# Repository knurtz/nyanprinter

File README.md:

# NyanPrinter
This printer runs on STM32F103 and it prints AND plays the nyan cat!

## Idea

Thermal printers make a lot of noise while printing -- everyone, who has bought something from a shop with one of those old cash registers knows that! At the heart of such a printer lies of course a stepper motor. Making music with stepper motors is an old thing in the Arduino community. But as far as I know, nobody has ever tried to make music AND print something at the same time -- until now!

Getting picture and sound to line up is not particulary easy, because there are certain limitations to the printing speed of a thermal printer -- and thus also for the maximum pitch we can get out of the machine. 

The datasheet recommends an approximate exposure of 1 ms per line, which responds to a 1 kHz pitch. This is, unless more than 64 pixels out of the total 384 pixels per line are printed simultanously. Here we need to do devided printing, which means multiple exposure bursts for one single line. This is where things get tricky. I need to let the printer run at a fixed speed and cannot stop at a line just because I want to print more than 64 pixels. Otherwise I would get a sudden break in my music.

This is the solution I came up with: If the printer encounters a line with more than 64 pixels, it prints the first 64 (or less) pixels, then advances the motor one step, going back one step immediately in order to print the next 64 pixels and so on. I have not yet tested, if the sudden change in direction is audible. If so, I might have to change it up a little bit and print multiple lines first, then go back over them a second time.

## Hardware

- STM32F103 Bluepill Development Board: [stm32duino.com](https://web.archive.org/web/20190524151648/https://wiki.stm32duino.com/index.php?title=Blue_Pill)
- Thermal printer MATSUSHITA EPL1801S2E from [pollin.de](https://www.pollin.de/p/thermo-druckelement-matsushita-epl1801s2e-721066)
- an awesome huge blue push button from [Amazon](https://www.amazon.de/gp/product/B07BSFMZJ2) (it lights up, too!)
- A4988 stepper motor driver board like this one from [pololu.com](https://www.pololu.com/product/1182)
- RECOM R-78E5.0-0.5 DC/DC converter from [conrad.de](https://www.conrad.de/de/recom-r-78e50-05-dcdc-wandler-print-24-vdc-5-vdc-500-ma-anzahl-ausgaenge-1-x-157954.html?)
- MAX6966 led driver from [farnell.com](https://de.farnell.com/maxim-integrated-products/max6966aee/led-treiber-mit-i-o-erweiterung/dp/2516036) for fancy led stuff
- custom milled PCB with some additional components like resistors and capacitors (Eagle files following shortly)
- custom enclosure printed with the amazing Vertigo Starlight filament from [filamentworld.de](https://www.filamentworld.de/shop/pla-filament-3d-drucker/pla-filament-1-75-mm-vertigo-starlight-075-kg/) (STL files following shortly as well)

## Software

I wanted to learn more about hardware peripherals of the STM32 family in this project. This is why I use a total of 3 timers, 2 DMA channels, one SPI and one UART peripheral. Things could have probably be done less complicated, but I would not have learned anything the easy way.

TIM2 is responsible for the motor step signal. It runs at a frequency that is determined by the current pitch of the music. The motor driver makes a step at every rising edge of the signal. Also, the printer needs to advance two steps for every line. Because of that, at every update interrupt of TIM2 (which corresponds to every step of the motor) I alternate between sending new data to the printer (triggering TIM1) and starting the exposure (triggering TIM3).

Data transfer is timed by TIM1, which triggers 64 DMA requests (64 transfers * 6 "pixels" per transfer = 384 pixels per line). The DMA sends the data to 6 parallel data lines that go into 6 shift registers inside the printer. Data alignment looks weird, this is why I wrote a small python script to convert images to a special byte array.

Finally TIM3 creates a pulse that corresponds to the needed exposure time of about 750 - 1000 us (depending on the supply voltage).

UART is needed for debugging and SPI for the led driver.

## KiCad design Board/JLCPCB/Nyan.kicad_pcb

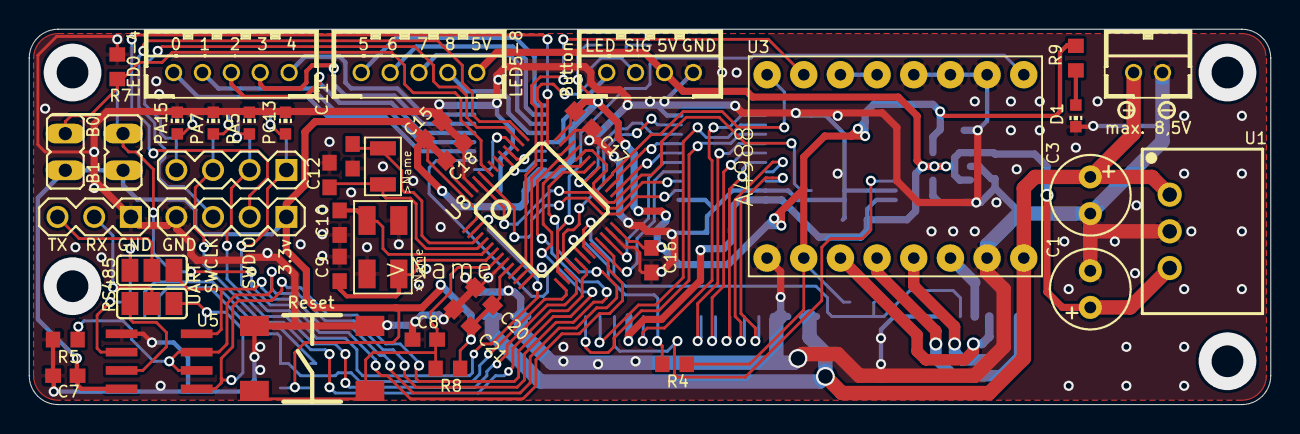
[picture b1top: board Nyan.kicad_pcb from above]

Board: 2 copper layers, 86.0 x 26.0 mm, 66 parts (0 on the bottom side), 75 nets.

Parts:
C1, C3: 100u; E2,5-6
C2, C14, C21: 1u; C0603
C4, C5, C6, C7, C8, C15, C16, C17, C18, C20, C22: 100n; C0603
C9, C10: 30p; C0603
C11, C12: 15p; C0603
C13: 22n; C0603
C19: 10u; C0603
D1, D2, D3, D4, D5: CHIP-LED0603
JP1, JP2: JP1
Q1: 8M; SMD_5X3.2
Q2: 32768; SMD_3.2X1.5
R1: 300; R0603
R2: 47k; R0603
R3, R4, R5, R6, R7, R8, R9, R10, R11, R12, R13, R14: 10k; R0603
S1: 6X6_MOMENTARY_SWITCH
SJ1, SJ2: SJ_2
SV2, SV3: MA04-1_ROUND
U1: R-78C5.0-1.0; SIP3
U2: SOT23-5
U3: A4988_STEP
U4: MAX6966; QSOP-16
U5: ST3485; SO-08
U6, U7: 74HCT541PW; TSSOP20
U8: STM32F10XCXT6; TQFP48
X1: WR-WTB2.0-2_THT-VER; WR-WTB2.0-2-THT-VER
X2: WR-WTB2.0-4_THT_VER; WR-WTB2.0-4-THT-VER
X3, X4: WR-WTB2.0-5_THT-VER; WR-WTB2.0-5-THT-VER
X5: MA03-1_ROUND
X6: 68610614122
X7: 68612414422
X8: 68610414122

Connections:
+3V3: C4.1, C7.2, C14.1, C15.2, C16.2, C17.2, C18.2, C19.2, C20.2, C21.2, JP1.2, JP2.2, R1.2, R2.2, R3.2, R4.2, R8.2, R9.2, R14.1, SV2.1, U2.5, U3.VDD, U4.16, U5.8, U8.1, U8.9, U8.24, U8.36, U8.48
+5V: C1.+, C2.1, C5.2, C6.2, U1.3, U2.1, U2.3, U6.20, U7.20, X2.2, X4.1, X7.14
+12V: C3.+, U1.1, U3.VMOT, X1.2, X7.1, X7.2, X7.23, X7.24
A/TX: SJ1.2, X5.3
B/RX: SJ2.2, X5.2
BOOT0: JP1.1, R7.2, U8.44
BOOT1: JP2.1, R6.2, U8.20
BUT_LED: U4.13, X2.4
BUT_SIG: C22.1, R14.2, U8.11, X2.3
D1: U6.2, U8.45
D1_5V: U6.18, X7.5
D2: U6.3, U8.46
D2_5V: U6.17, X7.6
D3: U6.4, U8.21
D3_5V: U6.16, X7.7
D4: U6.5, U8.22
D4_5V: U6.15, X7.8
D5: U6.6, U8.25
D5_5V: U6.14, X7.9
D6: U6.7, U8.26
D6_5V: U6.13, X7.17
DCLK: U6.8, U8.29
DCLK_5V: U6.12, X7.16
FREE_LED: U4.12, X4.2
GND: C1.-, C2.2, C3.-, C4.2, C5.1, C6.1, C7.1, C8.1, C9.2, C10.2, C11.2, C12.2, C13.2, C14.2, C15.1, C16.1, C17.1, C18.1, C19.1, C20.1, C21.1, C22.2, D1.C, D2.C, D3.C, D4.C, D5.C, Q1.2, Q1.4, R5.1, R6.1, R7.1, S1.3, S1.4, SV2.4, U1.2, U2.2, U3.GND, U3.GND2, U3.MS1, U3.MS2, U3.MS3, U4.8, U5.5, U6.1, U6.10, U6.19, U7.1, U7.10, U7.19, U8.8, U8.23, U8.35, U8.47, X1.1, X2.1, X5.1, X6.6, X7.3, X7.4, X7.21, X7.22, X8.2
HEAD_THERM: R4.1, U8.18, X7.12
LATCH: U7.2, U8.28, U8.32
LATCH_5V: U7.18, X7.15
LED1: U4.3, X3.5
LED2: U4.4, X3.4
LED3: U4.5, X3.3
LED4: U4.6, X3.2
LED5: U4.7, X3.1
LED6: U4.9, X4.5
LED7: U4.10, X4.4
LED8: U4.11, X4.3
LED_CLK: U4.1, U8.39
LED_CS: U4.2, U8.12
LED_MISO: U4.14, U8.40
LED_MOSI: U4.15, U8.41
M1A: U3.1A, X6.1
M1B: U3.1B, X6.3
M2A: U3.2A, X6.2
M2B: U3.2B, X6.4
MOT_DIR: U3.DIR, U8.27
MOT_EN: U3./EN, U8.14
MOT_STP: U3.STEP, U8.10
MOT_THERM: R3.1, U8.19, X6.5
unnamed: R1.1, X8.4
unnamed: U3./RST, U3./SLP
unnamed: C8.2, R8.1, S1.1, S1.2, U8.7
unnamed: C12.1, Q2.1, U8.4
unnamed: C11.1, Q2.2, U8.3
unnamed: C10.1, Q1.3, U8.5
unnamed: C9.1, Q1.1, U8.6
unnamed: D4.A, R12.1
unnamed: D1.A, R9.1
unnamed: D2.A, R10.1
unnamed: D3.A, R11.1
unnamed: C13.1, U2.4
unnamed: D5.A, R13.1
PA5: R11.2, SV3.2, U8.15
PA7: R12.2, SV3.3, U8.17
PA15: R13.2, SV3.4, U8.38
PC13: R10.2, SV3.1, U8.2
PHOTO: R2.1, U8.13, X8.3
RS485_A: SJ1.3, U5.6
RS485_B: SJ2.1, U5.7
RTS: R5.2, U5.2, U5.3, U8.33
RX: SJ2.3, U5.1, U8.31
STROBE: U6.9, U8.16
STROBE_5V: U6.11, X7.13
SWCLK: SV2.3, U8.37
SWDIO: SV2.2, U8.34
TX: SJ1.1, U5.4, U8.30

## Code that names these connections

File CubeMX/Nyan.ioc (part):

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Mcu.Name=STM32F103C(8-B)Tx
Mcu.Package=LQFP48
Mcu.UserName=STM32F103C8Tx
PA0-WKUP.GPIOParameters=GPIO_Label
PA0-WKUP.GPIO_Label=MOT_STP
PA0-WKUP.Signal=S_TIM2_CH1_ETR
PA1.GPIOParameters=GPIO_Label
PA1.GPIO_Label=BIG_BUTTON
PA1.Signal=GPIO_Input
PA10.Mode=Asynchronous
PA10.Signal=USART1_RX
PA11.GPIOParameters=GPIO_Label
PA11.GPIO_Label=LATCH
PA11.Signal=GPIO_Output
PA13.Mode=Serial_Wire
PA13.Signal=SYS_JTMS-SWDIO
PA14.Mode=Serial_Wire
PA14.Signal=SYS_JTCK-SWCLK
PA15.GPIOParameters=GPIO_Label
PA15.GPIO_Label=LED4
PA15.Signal=GPIO_Output
PA2.GPIOParameters=GPIO_Label
PA2.GPIO_Label=LED_CS
PA2.Signal=GPIO_Output
PA3.GPIOParameters=GPIO_Label
PA3.GPIO_Label=PHOTO
PA3.Signal=GPIO_Input
PA4.GPIOParameters=GPIO_Label
PA4.GPIO_Label=MOT_EN
PA4.Signal=GPIO_Output
PA5.GPIOParameters=GPIO_Label
PA5.GPIO_Label=LED2
PA5.Signal=GPIO_Output
PA6.GPIOParameters=GPIO_Label
PA6.GPIO_Label=STROBE
PA6.Signal=GPIO_Output
PA7.GPIOParameters=GPIO_Label
PA7.GPIO_Label=LED3
PA7.Signal=GPIO_Output
PA8.GPIOParameters=GPIO_Label
PA8.GPIO_Label=DCLK
PA8.Signal=GPIO_Output
PA9.Mode=Asynchronous
PA9.Signal=USART1_TX
PB0.GPIOParameters=GPIO_Label
PB0.GPIO_Label=HEAD_NTC
PB0.Signal=ADCx_IN8
PB1.GPIOParameters=GPIO_Label
PB1.GPIO_Label=MOT_NTC
PB1.Signal=ADCx_IN9
PB10.GPIOParameters=GPIO_Label
PB10.GPIO_Label=D3
PB10.Signal=GPIO_Output
PB11.GPIOParameters=GPIO_Label
PB11.GPIO_Label=D4
PB11.Signal=GPIO_Output
PB12.GPIOParameters=GPIO_Label
PB12.GPIO_Label=D5
PB12.Signal=GPIO_Output
PB13.GPIOParameters=GPIO_Label
PB13.GPIO_Label=D6
PB13.Signal=GPIO_Output
PB14.GPIOParameters=GPIO_Label
PB14.GPIO_Label=MOT_DIR
PB14.Signal=GPIO_Output
PB3.GPIOParameters=GPIO_Label
PB3.GPIO_Label=LED_CLK
PB3.Mode=Full_Duplex_Master
PB3.Signal=SPI1_SCK
PB4.GPIOParameters=GPIO_Label
PB4.GPIO_Label=LED_MISO
PB4.Mode=Full_Duplex_Master
PB4.Signal=SPI1_MISO
PB5.GPIOParameters=GPIO_Label
PB5.GPIO_Label=LED_MOSI
PB5.Mode=Full_Duplex_Master
PB5.Signal=SPI1_MOSI
PB8.GPIOParameters=GPIO_Label
PB8.GPIO_Label=D1
PB8.Signal=GPIO_Output
PB9.GPIOParameters=GPIO_Label
PB9.GPIO_Label=D2
PB9.Signal=GPIO_Output
PC13-TAMPER-RTC.GPIOParameters=GPIO_Label
PC13-TAMPER-RTC.GPIO_Label=LED1
PC13-TAMPER-RTC.Signal=GPIO_Output
RCC.SYSCLKFreq_VALUE=64000000
RCC.SYSCLKSource=RCC_SYSCLKSOURCE_PLLCLK
board=custom

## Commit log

2019-03-30 Code for initialising the timers done, basic picture format as 2d array set up
2019-04-01 Timer und DMA konfiguriert
2019-04-01 Datenblatt und Planungsdateien
2019-04-01 changed readme
2019-04-01 minor changed that didn't help te problem
2019-04-04 Motor dreht jetzt mit Timer PWM über CC1
2019-04-05 DMA transfer to GPIO works
2019-04-05 Python image analyzer copied from old Arduino project and modified for STM32 implementation
2019-04-05 Added some project information in readme.md
2019-04-05 Added printer name in readme
2019-04-05 Added image to code, test routine should work, doesn't :(
2019-04-05 Fixed something, but still not working. Probably because of voltage differences between STM and printer :(
2019-04-06 Eagle files for milled circuit board
2019-04-08 Current development state with hardware fixes for 3 to 5 volt level shifting
2019-04-11 Fixed PB4 being always high by disabling JTAG
2019-04-11 Everything in interrupt routine, no manual triggering anymore
2019-04-14 [Board] Copied board for manufacturing at JLCPCB. Big changes
2019-04-14 [Doku] Updated roadmap for new board (also english now)
2019-04-14 Added bluepill schematic as reference and STM32CubeMX Config files
2019-04-14 [Board] A little more layouting done
2019-04-22 [Board] Positioning done
2019-04-27 [Board] Fixed positions for half the components
2019-04-27 [Board] Fixed positioning done
2019-04-27 [Board] Some progress in routing
2019-04-27 [Board] Some more traces :)
2019-04-27 [Board] And even more traces
2019-04-28 [Board] More layouting done
2019-04-30 [Board] Layouting of first half (microcontroller side) done.
2019-05-01 [Board] More layouting
2019-05-03 [Board] almost complete, last gnd and 3v traces missing
2019-05-03 [Board] Layout done
2019-05-04 [Board] Silk Screen Top done
2019-05-04 [Board] Silk Screen Bottom done
2019-05-05 [Board] Silkscreen done, DRC checked
2019-05-05 [Board] Fixed connection for crystals
2019-05-06 [Board] Added debouncing circuitry for pushbutton
2019-05-06 [Board] Finished for manufacturing
2019-05-26 Project settings updated for Eclipse version 2019-03
2019-05-27 Moved a lot of functions to separate source files
2019-05-27 Minor tidy up
2019-05-28 Fixed misfiring interrupt. Test image works.
2019-05-28 [Converter] Added detection for too many black pixels
2019-06-04 Added function for pitch adjustment
2019-06-10 Corrected intentation for all files
2019-06-10 Added defines for note frequencies
2019-06-10 Counting down notes instead of up
2019-06-10 Test: Image data direction
2019-08-19 [Code] Separated image data into header and source files
2019-08-19 [Image Converter] Modified converter to support more than 64 pixels per line
2019-08-19 [Code] Small changes to support more than 64 pixels per line
2019-08-20 [Images] Added converted nyan images
2019-08-20 [Tone generation] Added preload feature for step timer, possibly fixing interrupted notes
2019-08-22 [Datasheets] Moved to separate folder, added MAX6966
2019-08-22 [Roadmap] Finally translated the rest of the file
2019-08-22 [SPI LED] Added defines and GPIO setup for SPI LED driver
2019-08-22 [STM32 Cube Config] Migrated to newer program version
2019-08-22 [SPI LED] Implemented initialization for SPI LED driver
2019-08-22 [Code] Added systick counter and interrupt to delay feature
2019-08-22 [Readme] Changed link to stm32duino.com to archive
2019-08-22 [Code] Added generator for breathing pattern
2019-08-22 [Code] Changed default motor direction
2019-08-22 [Code] Modified breathing pattern to accomodate minimum and maximum values of MAX6966 LED driver
2019-08-22 [Code] Removed left over declaration
2019-08-27 [Code] Fixed misspelled variable name
2019-08-27 [SPI LED] Breathing LED in main loop works
2019-08-27 [SPI LED] Changed breathing period to 4 seconds
2019-08-27 [SPI LED] 20 mA current for LEDs
2019-08-27 [Code] Added some rough features for music generation
2019-08-27 [Code] Changed image to nyan start
2019-08-31 [Code] Frame counter also counts down to avoid confusion
2019-08-31 [Code] Latch fixed active
2019-08-31 [Code] Back to working test image.
2019-09-02 [Test Immage] New test image, diagonal line
2019-09-02 [Code] Static offset to iamge buffer fixes misaligned line
2019-09-02 [Code] Back to nyan cat, 1/10th speed, finally a correct cat
2019-10-07 [Elipse Config] Language settings
2019-10-07 [Image Converter] Changed conerter so one line will always end after the first 64 colored pixels
2021-12-05 Added KiCAD for Bom
2021-12-05 Added CubeMX code
2021-12-19 Added timer for strobe
2021-12-19 Added photoshop file for printed image
